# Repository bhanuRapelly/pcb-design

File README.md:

# pcb-design
experimenting pcb design for ergo keyboard with blackpill

## PINS for ROW and COL
27 - ROW0
28 - COL1
29 - COL0
30 - ROW1

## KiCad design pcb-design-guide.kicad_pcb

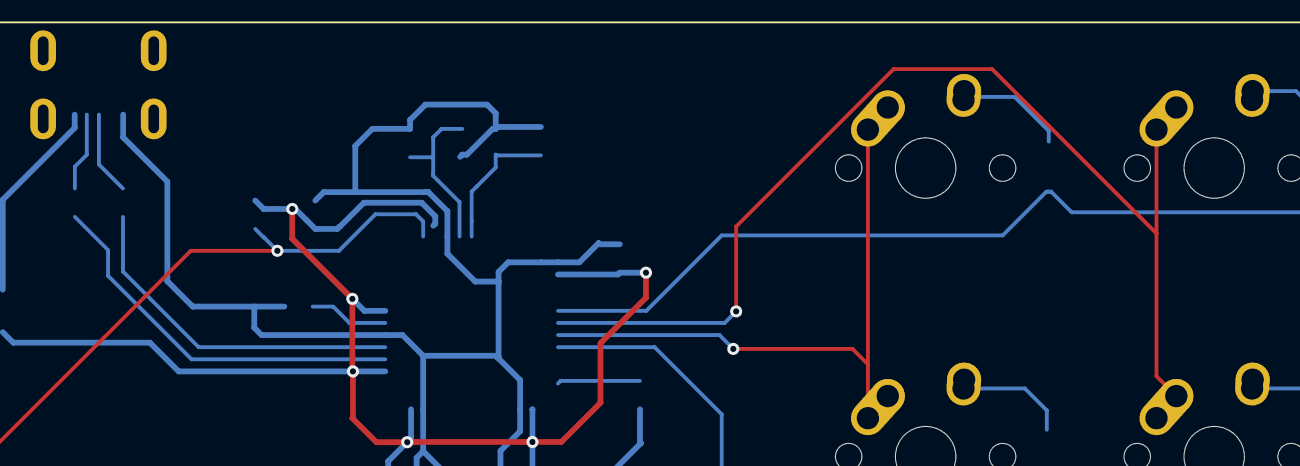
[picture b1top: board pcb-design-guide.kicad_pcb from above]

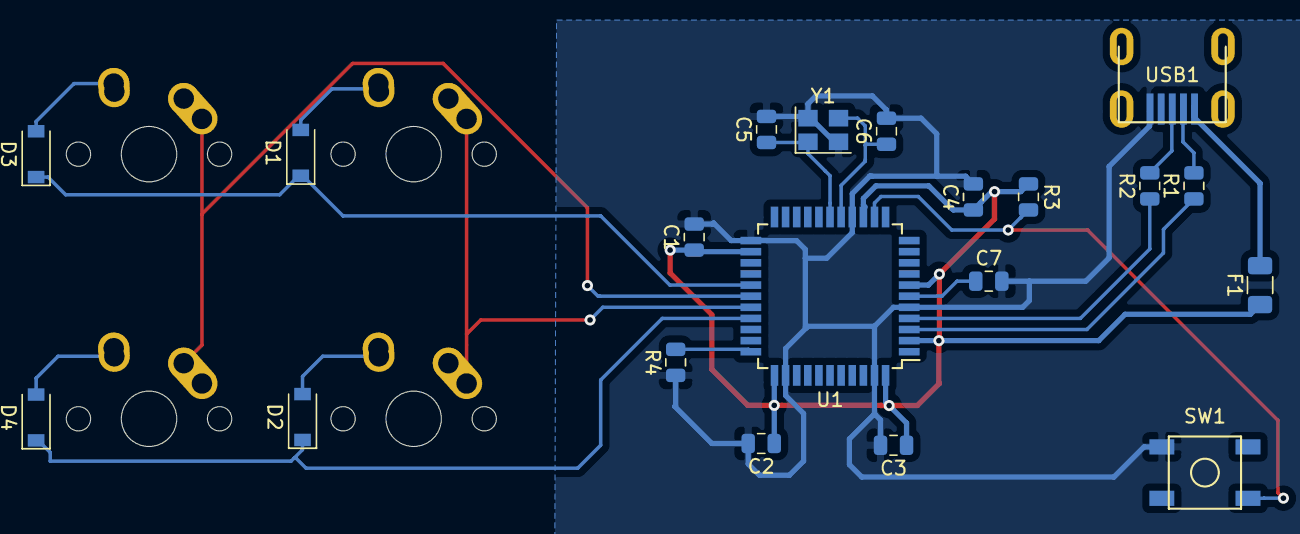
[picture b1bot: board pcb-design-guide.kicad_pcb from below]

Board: 2 copper layers, 24 parts (20 on the bottom side), 20 nets.

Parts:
C1, C2, C3, C4: 0.1uF; C_0805_2012Metric
C5, C6: 22pF; C_0805_2012Metric
C7: 1uF; C_0805_2012Metric
D1, D2, D3, D4: SOD-123; D_SOD-123
F1: 500mA; Fuse_1206_3216Metric
MX1, MX2, MX3, MX4: MX-NoLED; MX-1U-NoLED
R1, R2: 22; R_0805_2012Metric
R3, R4: 10k; R_0805_2012Metric
SW1: SW_Push; SKQG-1155865
U1: ATmega32U4-AU; TQFP-44_10x10mm_P0.8mm
USB1: Molex-0548190589
Y1: 16MHz; Crystal_SMD_3225-4Pin_3.2x2.5mm

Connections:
+5V: C1.1, C2.1, C3.1, C4.1, F1.1, R3.1, U1.2, U1.7, U1.14, U1.24, U1.34, U1.44
COL0: MX1.1, MX2.1, U1.29
COL1: MX3.1, MX4.1, U1.28
D+: R2.2, USB1.3
D-: R1.2, USB1.4
GND: C1.2, C2.2, C3.2, C4.2, C5.2, C6.2, C7.2, R4.1, SW1.1, U1.5, U1.15, U1.23, U1.35, U1.43, USB1.1, Y1.2, Y1.4
unnamed: C5.1, U1.17, Y1.1
unnamed: C6.1, U1.16, Y1.3
unnamed: C7.1, U1.6
unnamed: D1.2, MX1.2
unnamed: D2.2, MX2.2
unnamed: D3.2, MX3.2
unnamed: D4.2, MX4.2
unnamed: R1.1, U1.3
unnamed: R2.1, U1.4
unnamed: R3.2, SW1.2, U1.13
unnamed: R4.2, U1.33
ROW0: D1.1, D3.1, U1.27
ROW1: D2.1, D4.1, U1.30
VCC: F1.2, USB1.5

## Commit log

2022-06-02 Created a new project in kicad
2022-06-02 Added submodules
2022-06-02 Added libraries to project
2022-06-02 pcb circuit schematic complete
2022-06-02 added row and column labels to schematic
2022-06-02 Partial pcb design
2022-06-02 PCB design complete
2022-06-02 Added ground fills
